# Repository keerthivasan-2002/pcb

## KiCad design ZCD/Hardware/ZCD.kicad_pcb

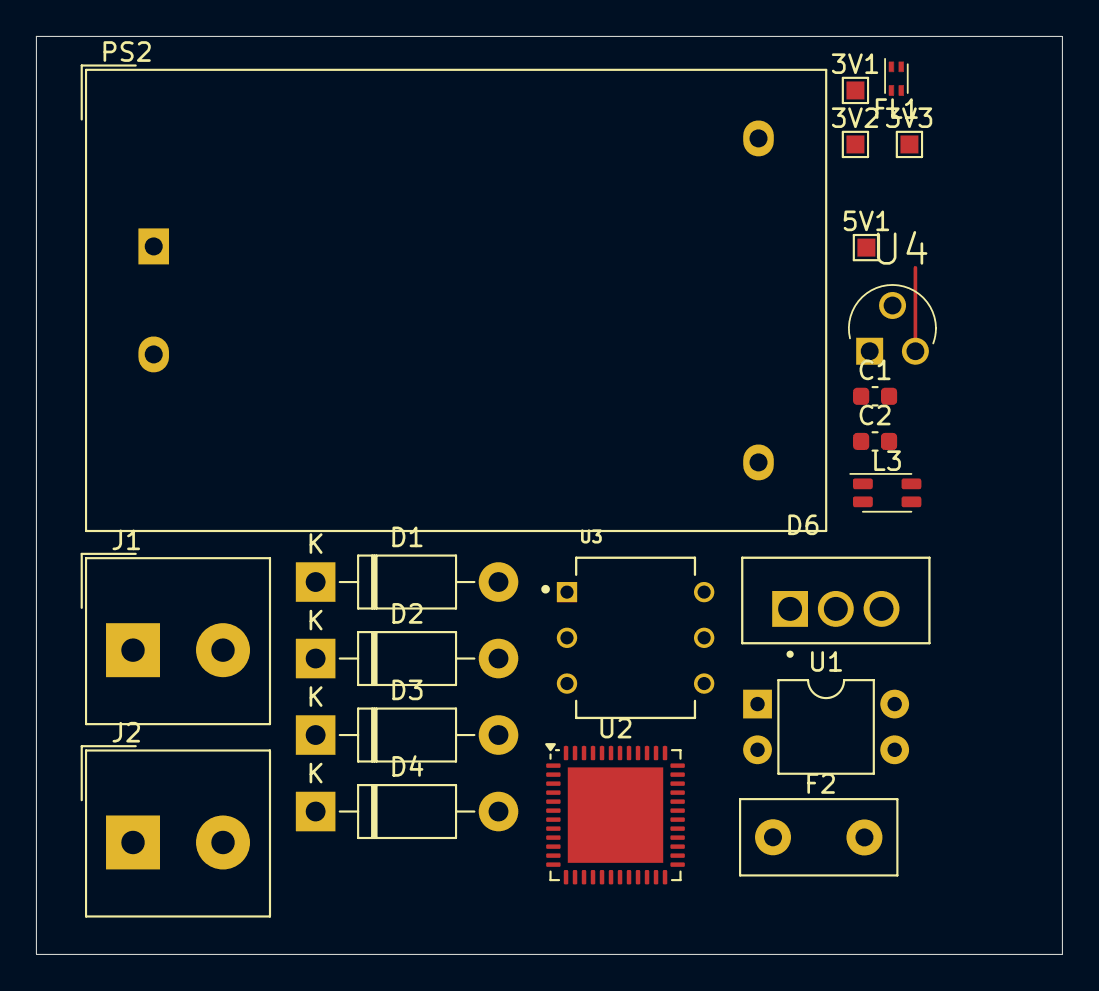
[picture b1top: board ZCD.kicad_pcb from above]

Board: 2 copper layers, 57.0 x 51.0 mm, 21 parts (0 on the bottom side), 13 nets.

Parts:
3V1, 3V2, 3V3: TP4; TestPoint_Pad_1.0x1.0mm
5V1: TP3; TestPoint_Pad_1.0x1.0mm
C1, C2: 1uF; C_0603_1608Metric
D1, D2, D3, D4: 1N4007; D_DO-41_SOD81_P10.16mm_Horizontal
D6: BT136-600E_127; BT136 -TRIAC
F2: 250Vac, 1A; Fuse_Littelfuse_395Series
FL1: Choke_Coilcraft_0603USB-142; L_CommonModeChoke_Coilcraft_0603USB
J1, J2: Screw_Terminal_01x02; Altech_AK100_1x02_P5.00mm
L3: Choke_Wurth_WE-CNSW_744232090; L_CommonMode_Wurth_WE-CNSW-1206
PS2: HLK-5M05; Converter_ACDC_Hi-Link_HLK-5Mxx
U1: PC817; DIP-4_W7.62mm
U2: ESP32-PICO-D4; QFN-48-1EP_7x7mm_P0.5mm_EP5.3x5.3mm
U3: MOC3021
U4: BC547B

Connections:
5V: 5V1.1, C1.1
+3V3: 3V1.1, 3V2.1, 3V3.1, C2.1, U1.4, U2.1 (VDDA), U2.43 (VDDA), U2.46 (VDDA)
GND: C1.2, C2.2, D3.2 (A), D4.2 (A), PS2.3 (-Vout), U1.2, U2.49 (GND), U3.2, U4.3 (E)
IO13: U2.20 (IO13), U4.1 (C)
NEUL: D6.3, FL1.4, J1.2, J2.1, U3.4
unnamed: F2.2, L3.1
unnamed: D1.2 (A), D3.1 (K), FL1.2
unnamed: D1.1 (K), D2.1 (K)
unnamed: D2.2 (A), D4.1 (K), FL1.3
unnamed: D6.1, J2.2
unnamed: L3.2, PS2.1 (AC/L)
unnamed: L3.3, PS2.2 (AC/N)
VAC: D6.2, FL1.1, J1.1

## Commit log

2024-12-16 first add
